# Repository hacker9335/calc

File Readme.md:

## Calculator

Calculator running on CircuitPython firmware with a Feather RP2040 with DVI output, driven by a 5x4 matrix keypad.
 
## Hardware
 
- Adafruit Feather RP2040 DVI 
- 5x4 matrix keypad, diodes pointing toward the columns (cathode at column, anode at row)
- HDMI/DVI display — tested target is a 7" 1024x600 panel, driven at 800x480 (panel scales it down)
  
## Keymap
 
```
x      ^      √      ÷
7      8      9      X
4      5      6      -
1      2      3      +
clear  0      .      sum
```
 
(`√` and `÷` show as the real symbols on-screen via the custom font which a extraction of the baisic one to preserve memory)

## Usage
 
**Basic math** — type a number, an operator, another number, then `sum` to evaluate. Chained expressions evaluate left to right
**`x` as a variable**
- `x 3 sum` → stores `3` into `x` (the screen shows `x=3`)
- `x + 5 sum` → substitutes the stored value of `x` into the expression
- Pressing `x` with nothing stored yet and using it in a calc shows an `x undef` error
**`√` (root)** — binary, first number is the degree, second is the radicand: `2 √ 9 sum` → `3` (square root of 9). `3 √ 27 sum` → cube root of 27.
 
**`clear`**
- single press → clears the current entry/expression only
- triple press within ~0.6s → also wipes the stored `x` value (shows `mem cleared`)

## Case
I dint yet make the display part of the case as im planning to do tht after i get it

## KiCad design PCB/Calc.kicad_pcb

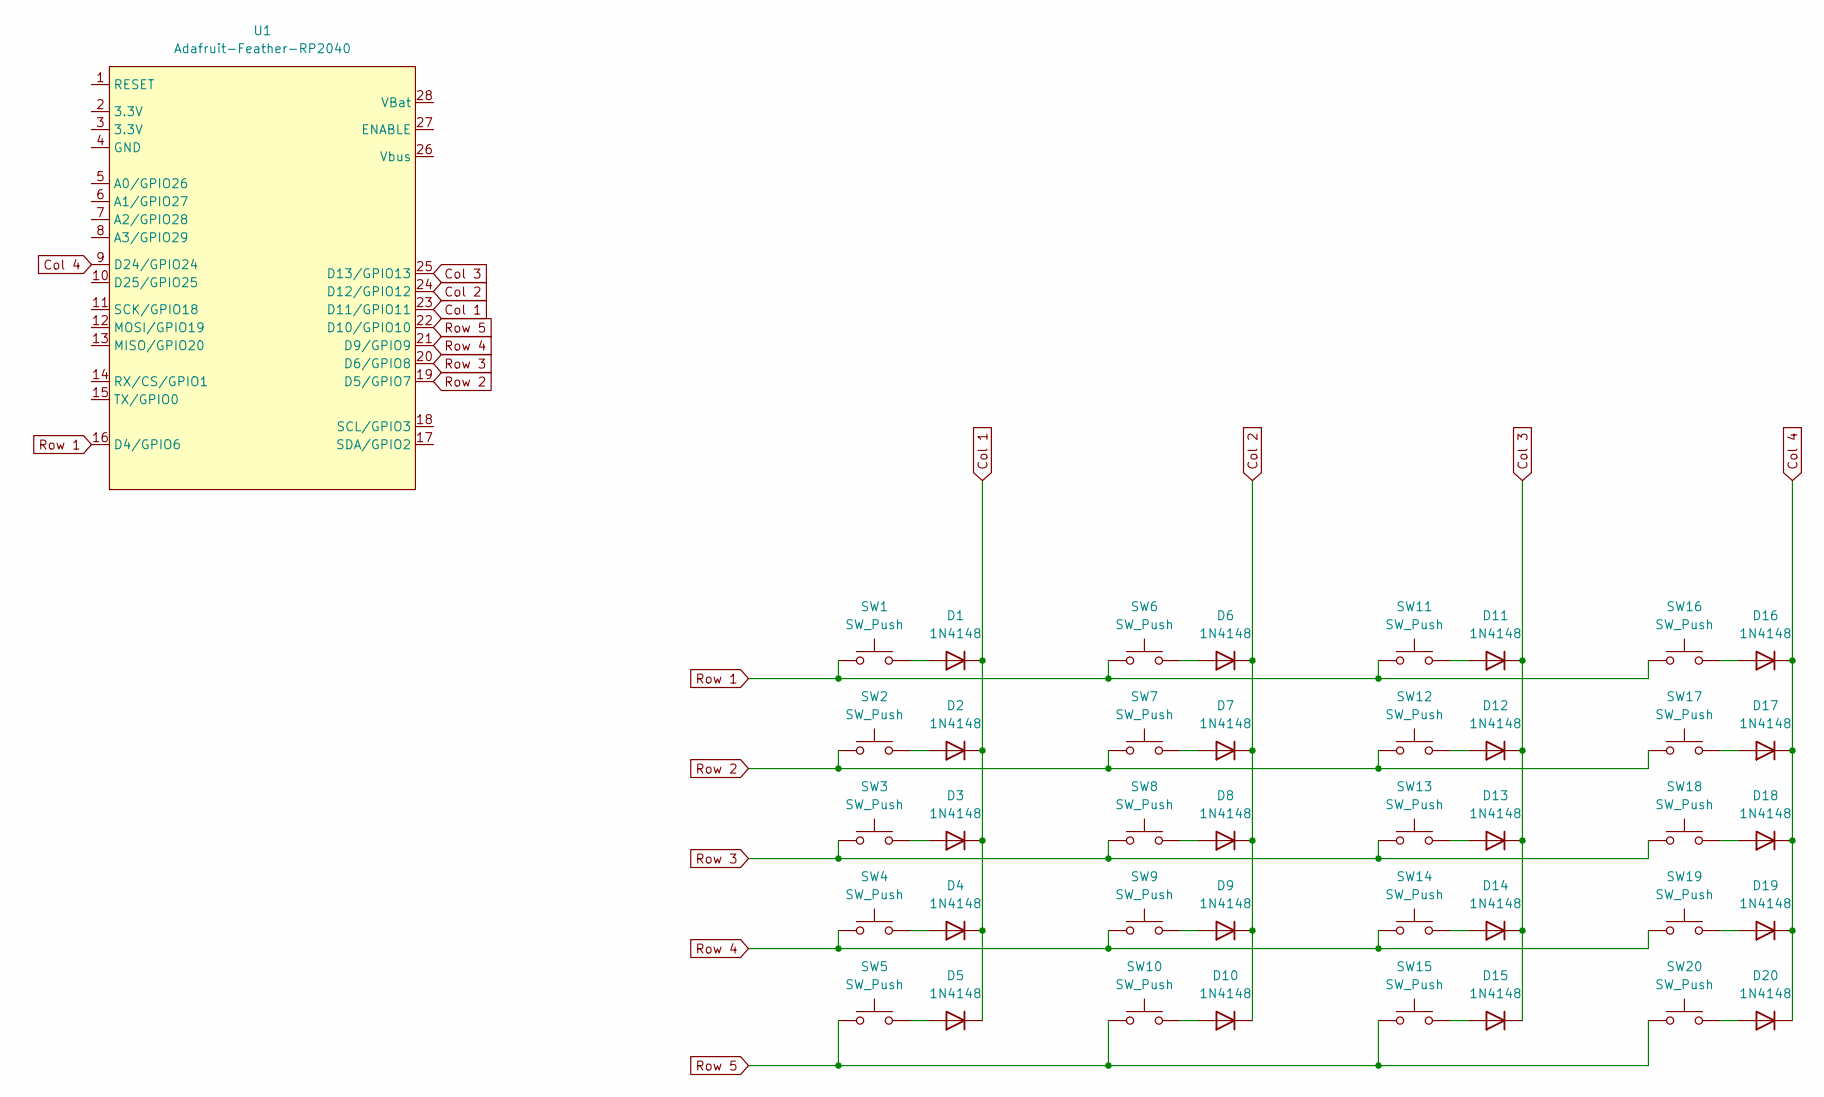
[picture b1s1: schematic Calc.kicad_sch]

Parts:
D1, D2, D3, D4, D5, D6, D7, D8, D9, D10, D11, D12, D13, D14, D15, D16, D17, D18, D19, D20: 1N4148; D_A-405_P12.70mm_Horizontal
SW1, SW2, SW3, SW4, SW5, SW6, SW7, SW8, SW9, SW10, SW11, SW12, SW13, SW14, SW15, SW16, SW17, SW18, SW19, SW20: SW_Push; SW_Cherry_MX_1.00u_PCB
U1: Adafruit-Feather-RP2040

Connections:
Col 1: D1.1 (K), D2.1 (K), D3.1 (K), D4.1 (K), D5.1 (K), U1.23 (D11/GPIO11)
Col 2: D6.1 (K), D7.1 (K), D8.1 (K), D9.1 (K), D10.1 (K), U1.24 (D12/GPIO12)
Col 3: D11.1 (K), D12.1 (K), D13.1 (K), D14.1 (K), D15.1 (K), U1.25 (D13/GPIO13)
Col 4: D16.1 (K), D17.1 (K), D18.1 (K), D19.1 (K), D20.1 (K), U1.9 (D24/GPIO24)
unnamed: D1.2 (A), SW1.2
unnamed: D2.2 (A), SW2.2
unnamed: D3.2 (A), SW3.2
unnamed: D4.2 (A), SW4.2
unnamed: D5.2 (A), SW5.2
unnamed: D6.2 (A), SW6.2
unnamed: D7.2 (A), SW7.2
unnamed: D8.2 (A), SW8.2
unnamed: D9.2 (A), SW9.2
unnamed: D10.2 (A), SW10.2
unnamed: D11.2 (A), SW11.2
unnamed: D12.2 (A), SW12.2
unnamed: D13.2 (A), SW13.2
unnamed: D14.2 (A), SW14.2
unnamed: D15.2 (A), SW15.2
unnamed: D16.2 (A), SW16.2
unnamed: D17.2 (A), SW17.2
unnamed: D18.2 (A), SW18.2
unnamed: D19.2 (A), SW19.2
unnamed: D20.2 (A), SW20.2
Row 1: SW1.1, SW6.1, SW11.1, SW16.1, U1.16 (D4/GPIO6)
Row 2: SW2.1, SW7.1, SW12.1, SW17.1, U1.19 (D5/GPIO7)
Row 3: SW3.1, SW8.1, SW13.1, SW18.1, U1.20 (D6/GPIO8)
Row 4: SW4.1, SW9.1, SW14.1, SW19.1, U1.21 (D9/GPIO9)
Row 5: SW5.1, SW10.1, SW15.1, SW20.1, U1.22 (D10/GPIO10)

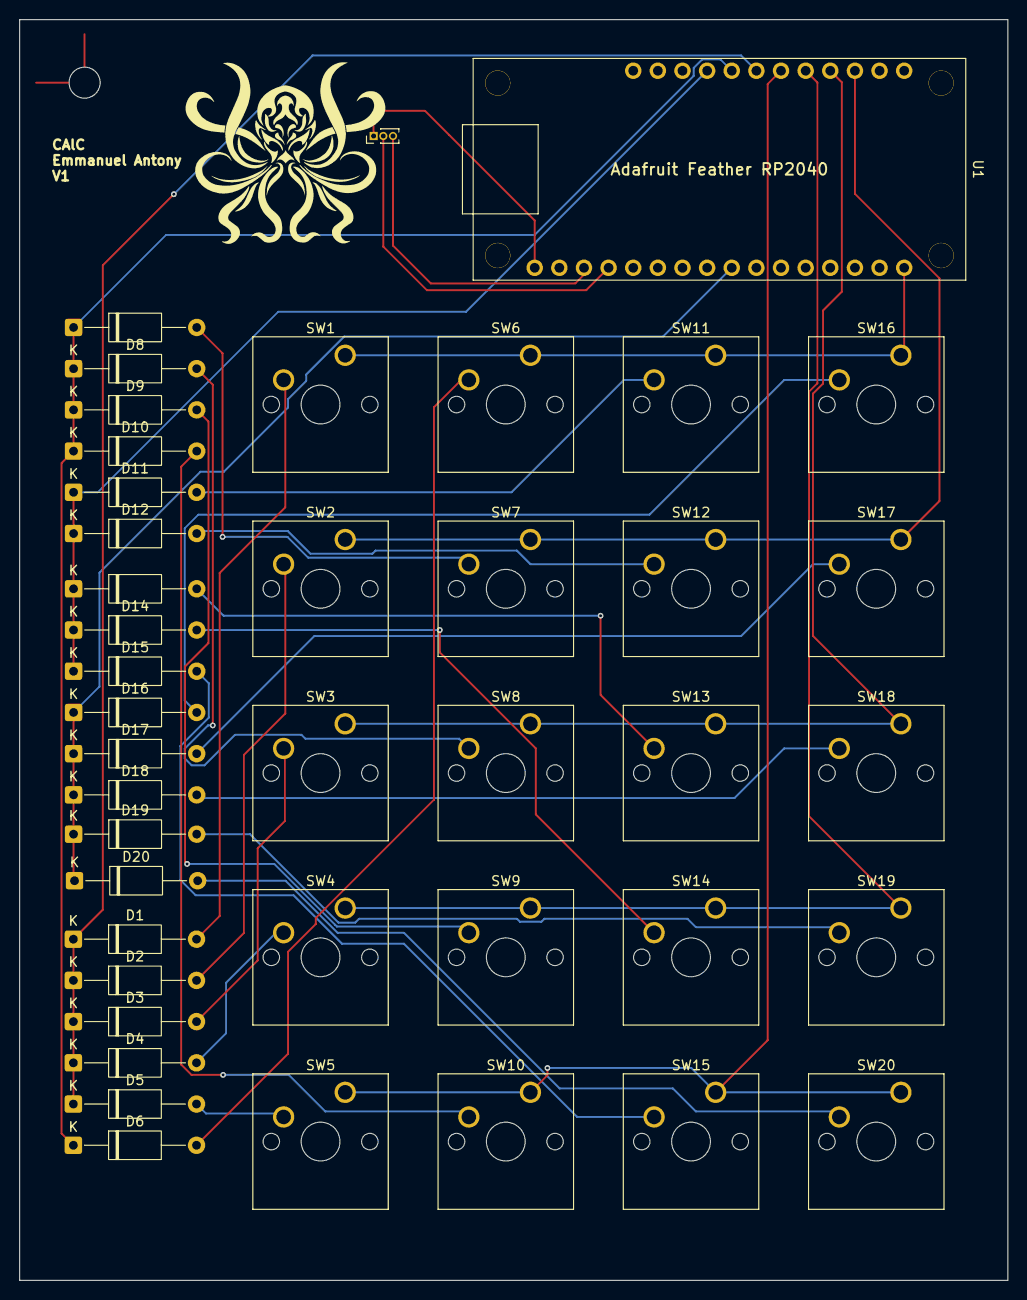
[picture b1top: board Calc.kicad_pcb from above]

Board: 2 copper layers, 101.9 x 130.0 mm, 41 parts (0 on the bottom side), 29 nets.

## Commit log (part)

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2026-06-21 push
    push
2026-06-21 Add README for CircuitPython calculator firmware
    Added detailed information about the CircuitPython calculator firmware, including hardware specifications, keymap, usage instructions, and case design.
2026-06-21 Fix formatting and content in README.md
    Updated the README to correct formatting and improve clarity.
2026-06-21 Create BOM.md with item list and pricing
    Added a Bill of Materials (BOM) with item details, quantities, links, and prices.
